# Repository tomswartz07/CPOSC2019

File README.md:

# CPOSC 2019: Open Circuit: PCBs and Free Software

## About

This repository contains the information and details related to
the CPOSC 2019 talk:

**Open Circuit: Printed Circuit Boards and Free Software**

This talk will provide a crash-course in open-source printed circuit design,
giving an overview of the entire process, from ideas in your brain to production.
The talk will cover topics such as Electronic Design Automation with KiCAD,
to circuit optimization, to generating gerber files for factory production.

## Learning Objectives
Audience will learn how to design and produce printed circuit boards
for use in various projects.
For example, this will help the intermediate-level Arduino project
developer produce circuit boards based on their breadboard designs.

The ideal audience member is someone who is familiar with circuit
design, even at a basic level.

## Session Outline
- Introduction: Why Make Circuit Boards?
- Designing a Schematic
- Creating a PCB Layout
- Generating Files for Factory Production
- Discussion of Factory Production

## Expectations for Attendees
Attendees will gain knowledge necessary to create their own Printed Circuit Boards,
knowing that it's not as difficult or scary as it may seem.

## Files in this Repository:

- `presentation/cposc2019.tex`: LaTeX Beamer presentation files
- `rbp140-kicad/`: Directory containing referenced KiCAD project files.

## Making the presentation

Assuming you have `pdflatex` installed, or TeXLive 2019-
simply run the following command:

```sh
cd presentation
pdflatex cposc2019.tex
```

The PDF document will be generated and viewable for you.

## Loading the KiCAD project

Assuming you have KiCAD installed, simply
navigate to `File` -> `Open Existing Project...` and select the project
directory.

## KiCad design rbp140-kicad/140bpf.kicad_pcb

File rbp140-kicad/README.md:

## 140 MHz Band-Pass Filter KiCAD PCB Files

This repository contains the files associated with the creation of a 
Band-Pass Filter ideal for NOAA APT Satellite and UHF Amateur Radio reception.

### Bill of Materials
- SMA PCB Mount connectors, available from various online sellers
  - Specific to this project, SMA Female Jack Right Angle PCB Mount RF Connectors were used
- [140-BPF+ chip from MiniCircuits](https://www.minicircuits.com/WebStore/dashboard.html?model=RBP-140%2B)

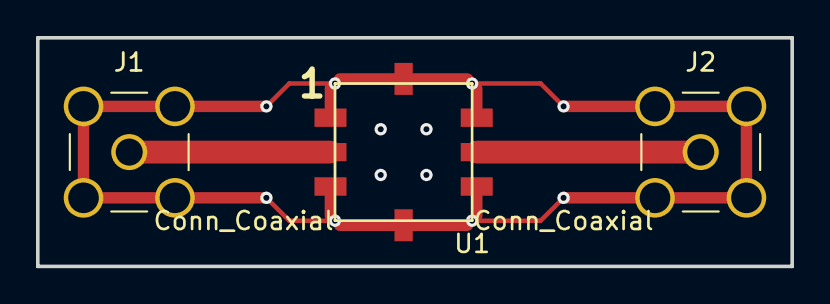
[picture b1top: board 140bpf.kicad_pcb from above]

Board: 2 copper layers, 41.9 x 12.7 mm, 3 parts (0 on the bottom side), 3 nets.

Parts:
J1, J2: Conn_Coaxial; SMA_THT_Jack_Straight
U1: RBP-140+

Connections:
GND: J1.2, J2.2, U1.1, U1.3, U1.4, U1.5, U1.7, U1.8
unnamed: J1.1, U1.2
unnamed: J2.1, U1.6

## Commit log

2019-08-18 Add Initial README
2019-08-18 Initial presentation files
2019-09-14 Incremental updates, add images
2019-09-19 Final major revisions of talk
2019-09-19 Add KiCAD Example Project Files
2019-09-20 Add clarifying text
2019-09-20 Add fix for mirrored text, version update
2019-09-25 Add schematic README
